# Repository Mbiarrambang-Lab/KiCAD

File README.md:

# KiCAD
this repository serves to keep all electrical PCBs schematics and Gerber files

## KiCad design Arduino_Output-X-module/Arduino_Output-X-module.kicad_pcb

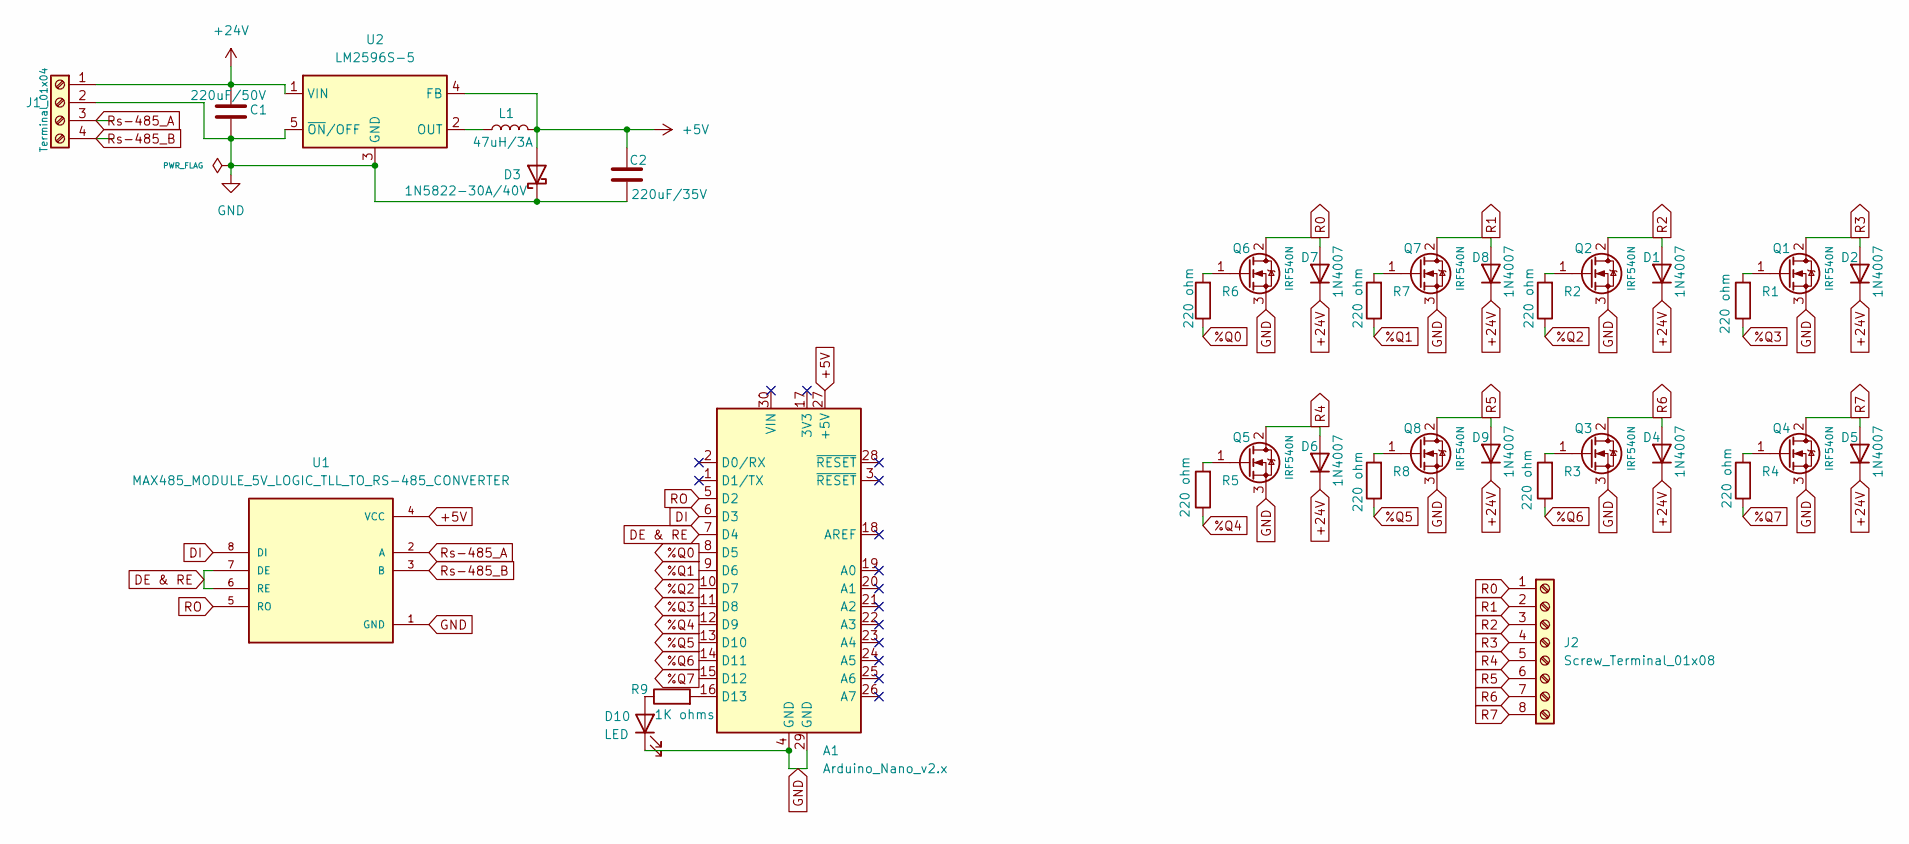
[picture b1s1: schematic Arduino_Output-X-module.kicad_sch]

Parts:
A1: Arduino_Nano_v2.x; Arduino_Nano
C1: 220uF/50V; CP_Radial_D10.0mm_P5.00mm
C2: 220uF/35V; CP_Radial_D8.0mm_P3.80mm
D1, D2, D4, D5, D6, D7, D8, D9: 1N4007; D_DO-41_SOD81_P10.16mm_Horizontal
D3: 1N5822-30A/40V; D_DO-201AD_P15.24mm_Horizontal
D10: LED; LED_D1.8mm_Horizontal_06.35mm_Z16.0mm
J1: Terminal_01x04; IDC-Header_2x04_P2.54mm_Horizontal
J2: Screw_Terminal_01x08; PhoenixContact_GMSTBA_2,5_8-G_1x08_P7.50mm_Horizontal
L1: 47uH/3A; L_Radial_D10.0mm_P5.00mm_Fastron_07M
Q1, Q2, Q3, Q4, Q5, Q6, Q7, Q8: IRF540N; TO-220-3_Vertical
R1, R2, R3, R4, R5, R6, R7, R8: 220 ohm; R_Axial_DIN0207_L6.3mm_D2.5mm_P2.54mm_Vertical
R9: 1K ohms; R_Axial_DIN0207_L6.3mm_D2.5mm_P2.54mm_Vertical
U1: MAX485_MODULE_5V_LOGIC_TLL_TO_RS-485_CONVERTER; MODULE_MAX485_MODULE_5V_LOGIC_TLL_TO_RS-485_CONVERTER; PARTREV 1r0
U2: LM2596S-5; TO-264-5_Vertical

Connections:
%Q0: A1.8 (D5), R6.1
%Q1: A1.9 (D6), R7.1
%Q2: A1.10 (D7), R2.1
%Q3: A1.11 (D8), R1.1
%Q4: A1.12 (D9), R5.1
%Q5: A1.13 (D10), R8.1
%Q6: A1.14 (D11), R3.1
%Q7: A1.15 (D12), R4.1
+5V: A1.27 (+5V), C2.1, D3.2 (A), L1.2, U1.4 (VCC), U2.4 (FB)
+24V: C1.1, D1.1 (K), D2.1 (K), D4.1 (K), D5.1 (K), D6.1 (K), D7.1 (K), D8.1 (K), D9.1 (K), J1.1, U2.1 (VIN)
DE & RE: A1.7 (D4), U1.6 (RE), U1.7 (DE)
DI: A1.6 (D3), U1.8 (DI)
GND: A1.4 (GND), A1.29 (GND), C1.2, C2.2, D3.1 (K), D10.1 (K), J1.2, Q1.3 (S), Q2.3 (S), Q3.3 (S), Q4.3 (S), Q5.3 (S), Q6.3 (S), Q7.3 (S), Q8.3 (S), U1.1 (GND), U2.3 (GND), U2.5 (~ON/OFF)
unnamed: A1.16 (D13), R9.2
unnamed: D10.2 (A), R9.1
unnamed: Q1.1 (G), R1.2
unnamed: Q2.1 (G), R2.2
unnamed: Q3.1 (G), R3.2
unnamed: Q4.1 (G), R4.2
unnamed: Q5.1 (G), R5.2
unnamed: Q6.1 (G), R6.2
unnamed: Q7.1 (G), R7.2
unnamed: Q8.1 (G), R8.2
unnamed: L1.1, U2.2 (OUT)
R0: D7.2 (A), J2.1, Q6.2 (D)
R1: D8.2 (A), J2.2, Q7.2 (D)
R2: D1.2 (A), J2.3, Q2.2 (D)
R3: D2.2 (A), J2.4, Q1.2 (D)
R4: D6.2 (A), J2.5, Q5.2 (D)
R5: D9.2 (A), J2.6, Q8.2 (D)
R6: D4.2 (A), J2.7, Q3.2 (D)
R7: D5.2 (A), J2.8, Q4.2 (D)
RO: A1.5 (D2), U1.5 (RO)
Rs-485_A: J1.3, U1.2 (A)
Rs-485_B: J1.4, U1.3 (B)

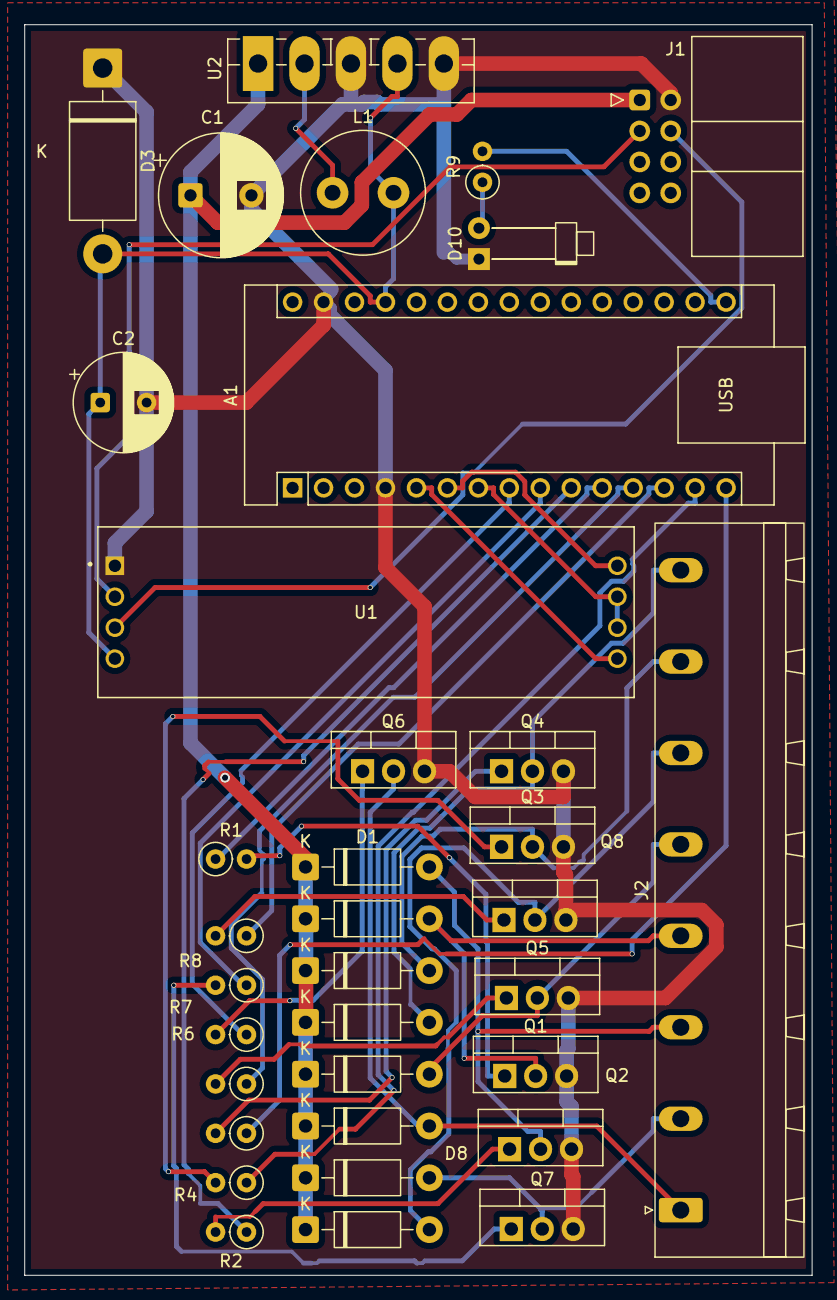
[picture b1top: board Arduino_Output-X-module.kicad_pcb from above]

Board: 2 copper layers, 64.6 x 102.6 mm, 35 parts (0 on the bottom side), 35 nets.
